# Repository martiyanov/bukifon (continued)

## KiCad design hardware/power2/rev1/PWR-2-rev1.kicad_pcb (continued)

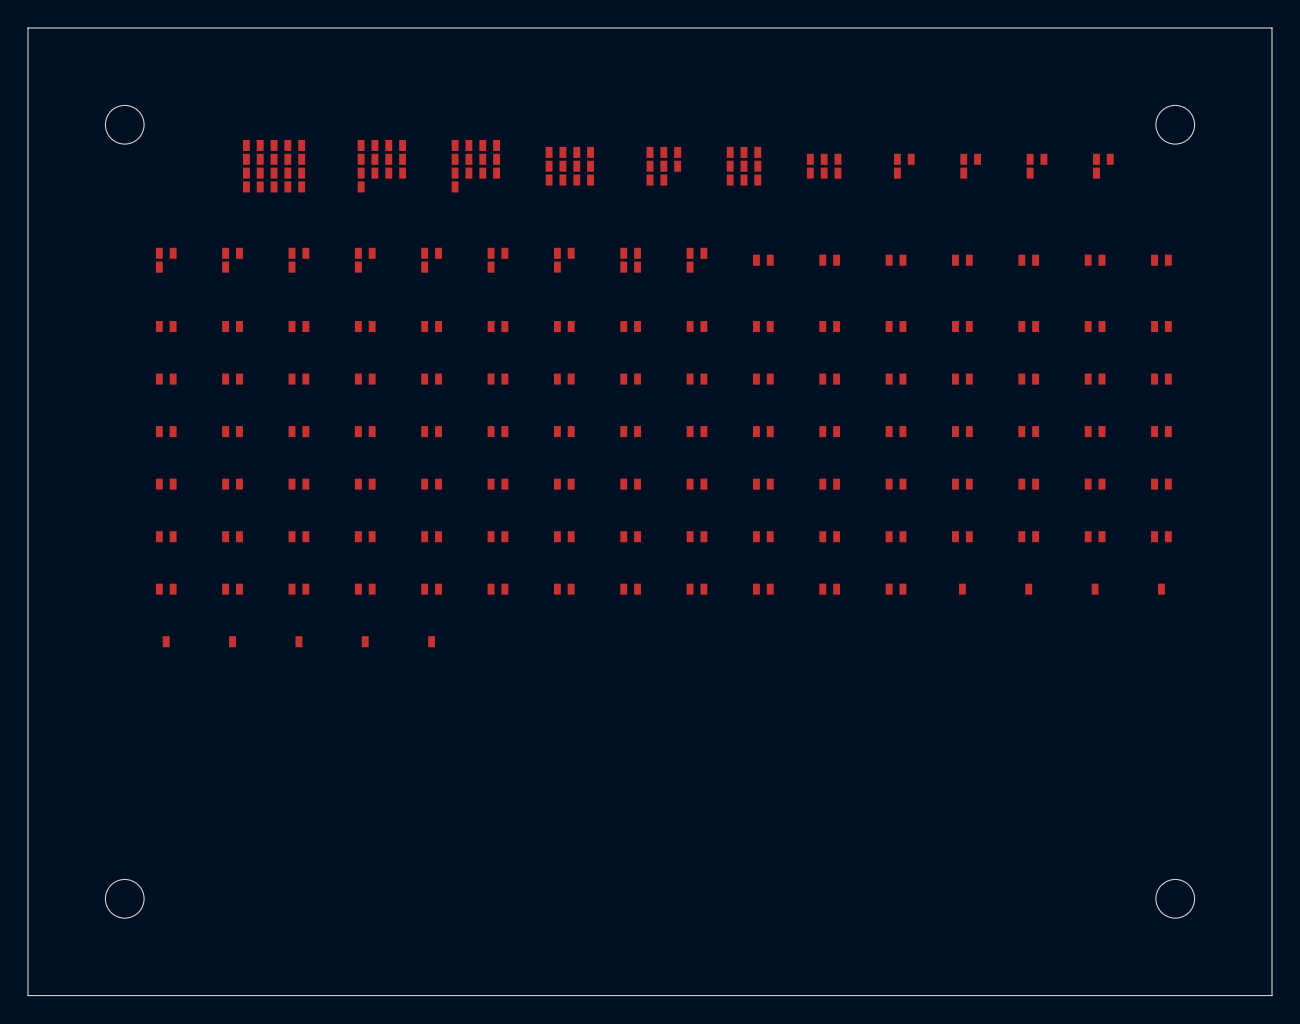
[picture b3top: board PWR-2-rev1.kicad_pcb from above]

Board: 4 copper layers, 90.0 x 70.0 mm, 132 parts (0 on the bottom side), 60 nets, no tracks yet.

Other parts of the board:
H1, H2, H3, H4: MountingHole; MountingHole_M2.5_2.8mm

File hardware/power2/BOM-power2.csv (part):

Артикул;MPN;Номинал;Кол-во;Позиции;Корпус;Примечание
PM-PWR2-001;;PACK 3P;1;J1;TerminalBlock_4Ucon_1x03_P3.50mm_Vertical;батарейный отсек: 1=B+, 2=B-, 3=NTC (термистор на банке)
PM-PWR2-002;;18650 3.6V 3.5Ah;1;BT1;BatteryHolder_Keystone_1042_1x18650;"банка 1/2 (параллель); холдер в батарейном отсеке, не на плате; off-board (battery/thermistor, вне платы)"
PM-PWR2-003;;18650 3.6V 3.5Ah;1;BT2;BatteryHolder_Keystone_1042_1x18650;"банка 2/2 (параллель); ХОЛДЕРЫ С КЛЮЧОМ от переполюсовки; off-board (battery/thermistor, вне платы)"
PM-PWR2-004;;5 A;1;F1;Fuse_1206_3216Metric;предохранитель пакета 4-5 А (по ТЗ): защита от КЗ и от переполюсовки одной банки
PM-PWR2-005;;AO3401A P-FET;1;Q1;SOT-23;защита от переполюсовки пакета: body diode PACK_F->VBAT (норма), reverse blocked
PM-PWR2-006;;100k;1;R1;R_0603_1608Metric;gate-source Q1: OFF при обрыве, ON при нормальной полярности (Vgs = -Vpack)
PM-PWR2-007;SMBJ5.0A;SMBJ5.0A;1;D1;D_SMA;TVS на пакете (ESD/импульсы при hot-plug)
PM-PWR2-008;;NTC 10k B3950;1;TH1;— (вне платы);"термистор на банке: -> TS BQ24074 (CORE-2) и -> CH7 (TEMP_MON); off-board (battery/thermistor, вне платы)"
PM-PWR2-009;;100R;1;R2;R_0603_1608Metric;RC-фильтр BAT BQ297xy
PM-PWR2-010;;100n;1;C1;C_0805_2012Metric;RC-фильтр BAT BQ297xy
PM-PWR2-011;;1k;1;R3;R_0603_1608Metric;токовый сенс BQ297xy (V-) к P-
PM-PWR2-012;BQ29700DSER (1S, OVP 4.275 В);BQ297xy;1;U1;SOT-23-6;BMS 1S: OVP 4.25-4.30 В, UVP 2.35-2.50 В, OCP/SCP (внешние NMOS)
PM-PWR2-013;AO3400A (N-FET 30 В);AO3400A;1;Q2;SOT-23;разрядный ключ BMS (общий исток с Q3)
PM-PWR2-014;AO3400A (N-FET 30 В);AO3400A;1;Q3;SOT-23;зарядный ключ BMS (общий исток с Q2)
PM-PWR2-015;;100k;1;R4;R_0603_1608Metric;gate-source Q2
PM-PWR2-016;;100k;1;R5;R_0603_1608Metric;gate-source Q3
PM-PWR2-017;;AO3401A P-FET;1;Q4;SOT-23;back-to-back P-FET 1/2 (reverse blocking, 11 мОм-класс)
PM-PWR2-018;;AO3401A P-FET;1;Q5;SOT-23;back-to-back P-FET 2/2
PM-PWR2-019;;100k;1;R6;R_0603_1608Metric;подтяжка затворов (OFF)
PM-PWR2-020;MMBT3904;MMBT3904;1;Q6;SOT-23;драйвер высокого плеча: ON = затворы к PGND
PM-PWR2-021;;10k;1;R7;R_0603_1608Metric;база Q6
PM-PWR2-022;;100k;1;R8;R_0603_1608Metric;база Q6 -> PGND (OFF по умолчанию)
PM-PWR2-023;;100k;1;R9;R_0603_1608Metric;MASTER_SW -> PGND (обрыв = OFF)
PM-PWR2-024;;100n;1;C2;C_0805_2012Metric;gate-source Q4/Q5: медленный пуск (inrush control)
PM-PWR2-025;;SW panel;1;J2;PinHeader_1x02_P2.54mm_Vertical;вывод на панельный тумблер питания (параллельно SW1)
PM-PWR2-026;;POWER OFF/ON;1;SW1;— (вне платы);местный слайдер питания (запасной/для макета)
PM-PWR2-027;SMBJ5.0A;SMBJ5.0A;1;D2;D_SMA;TVS после load switch
PM-PWR2-028;;22uF;1;C3;C_1210_3225Metric;вход всех преобразователей
PM-PWR2-029;MAX17048G+T (TDFN-8);MAX17048;1;U2;SOT-23-6;"fuel gauge 1S, I2C 0x36, +-7.5 мВ, без шунта; VDD = Kelvin на банку"
PM-PWR2-030;;10R;1;R10;R_0603_1608Metric;Kelvin-питание/сенс банки для гейджа (ток ~25 мкА)
PM-PWR2-031;;1uF;1;C4;C_0805_2012Metric;VDD гейджа
PM-PWR2-032;;100n;1;C5;C_0805_2012Metric;VDD гейджа ВЧ
PM-PWR2-033;;22R;1;R11;R_0603_1608Metric;серия I2C SDA (защита/развязка от длинного кабеля)
PM-PWR2-034;;22R;1;R12;R_0603_1608Metric;серия I2C SCL
PM-PWR2-035;;1k;1;R13;R_0603_1608Metric;резервный аналоговый контроль: сырой VBAT -> делитель CH6 на CORE-2
PM-PWR2-036;TPS61088RHLR (QFN-20);TPS61088;1;U3;QFN-20-1EP_3x3mm_P0.4mm_EP1.65x1.65mm;sync boost 10-A ключ: +12.15 В / 330 мА (запас 4x по току)
PM-PWR2-037;;10uH / 4A;1;L1;L_Bourns_SRN6045TA;индуктор +12 В (Isat >= 4 А)
PM-PWR2-038;;22uF;1;C6;C_1210_3225Metric;вход +12 В
PM-PWR2-039;;22uF;1;C7;C_1210_3225Metric;вход +12 В
PM-PWR2-040;;100n;1;C8;C_0805_2012Metric;вход +12 В ВЧ
PM-PWR2-041;;100k;1;R14;R_0603_1608Metric;ОС: Vout = 1.204*(1+100k/11k) = 12.15 В
PM-PWR2-042;;11k;1;R15;R_0603_1608Metric;низ ОС +12 В
PM-PWR2-043;;100n;1;C9;C_0805_2012Metric;soft-start +12 В
PM-PWR2-044;;100k;1;R16;R_0603_1608Metric;EN +12 В по умолчанию ON (pull-up в домене VSYS)
PM-PWR2-045;2N7002;2N7002;1;Q9;SOT-23;ключ EN +12 В: высокий уровень с CORE-2 (3.3 В) выключает рельс
PM-PWR2-046;;100n;1;C35;C_0805_2012Metric;фильтр EN +12 В
PM-PWR2-047;;4.7uH;1;L2;L_Bourns_SRN6045TA;pi-фильтр +12 В: L
PM-PWR2-048;;47uF/25V;1;C10;CP_Elec_6.3x7.7;pi-фильтр +12 В: C1
PM-PWR2-049;;47uF/25V;1;C11;CP_Elec_6.3x7.7;pi-фильтр +12 В: C2
PM-PWR2-050;;100n;1;C12;C_0805_2012Metric;pi-фильтр +12 В: HF
PM-PWR2-051;;0.5 A;1;F2;Fuse_1206_3216Metric;полифьюз шины +12 В (шина модулей <= 300 мА)
PM-PWR2-052;;SS34;1;D7;D_SMA;"последовательный SS34: защита от back-feed внешнего 12 В/шины; батарея не разряжается"
PM-PWR2-053;SMAJ15A;SMAJ15A;1;D3;D_SMA;TVS шины +12 В
PM-PWR2-054;;4.7k;1;R17;R_0603_1608Metric;разрядный резистор +12 В
PM-PWR2-055;;100n;1;C13;C_0805_2012Metric;ВЧ на шине +12 В
PM-PWR2-056;LMR33630ADDA (SOIC-8 PowerPAD, 36 В);LMR33630;1;U4;SOIC-8_3.9x4.9mm_P1.27mm;синхронный buck в инвертирующем IBB: GND МС = -12 В, VIN = VSYS+12 В = 15.7 В
PM-PWR2-057;;22uH / 2A;1;L3;L_Bourns_SRN6045TA;IBB: индуктор SW -> PGND (выход buck = системная земля)
PM-PWR2-058;;100n;1;C14;C_0805_2012Metric;bootstrap -12 В
PM-PWR2-059;;1uF;1;C15;C_0805_2012Metric;VCC МС (внутр. LDO) -> GND МС
PM-PWR2-060;;22uF/25V;1;C16;C_1210_3225Metric;вход IBB: 15.7 В (25 В керамика!)
PM-PWR2-061;;100n;1;C17;C_0805_2012Metric;вход IBB ВЧ
PM-PWR2-062;;22uF/25V;1;C18;C_1210_3225Metric;выход IBB 1
PM-PWR2-063;;22uF/25V;1;C19;C_1210_3225Metric;выход IBB 2
PM-PWR2-064;;110k;1;R19;R_0603_1608Metric;ОС IBB: Vout = 1.0*(1+110k/10k) = 12.0 В
PM-PWR2-065;;10k;1;R20;R_0603_1608Metric;низ ОС -12 В
PM-PWR2-066;PC817C (DIP-4);PC817;1;U5;DIP-4_W7.62mm;"оптопара: EN из домена PGND (3.3 В) в домен -12 В; транзистор тянет EN к GND МС"
PM-PWR2-067;;1k;1;R21;R_0603_1608Metric;ток LED оптопары ~2.1 мА
PM-PWR2-068;;100k;1;R22;R_0603_1608Metric;LED оптопары OFF при обрыве входа
PM-PWR2-069;;100k;1;R23;R_0603_1608Metric;EN -12 В по умолчанию ON (pull-up к VIN МС = 15.7 В)
PM-PWR2-070;;100n;1;C20;C_0805_2012Metric;фильтр EN -12 В
PM-PWR2-071;;10uH;1;L4;L_Bourns_SRN6045TA;pi-фильтр -12 В: L
PM-PWR2-072;;47uF/25V;1;C21;CP_Elec_6.3x7.7;pi-фильтр -12 В: C1
PM-PWR2-073;;47uF/25V;1;C22;CP_Elec_6.3x7.7;pi-фильтр -12 В: C2
PM-PWR2-074;;100n;1;C23;C_0805_2012Metric;pi-фильтр -12 В: HF
PM-PWR2-075;;0.3 A;1;F3;Fuse_1206_3216Metric;полифьюз -12 В (шина <= 95 мА)
PM-PWR2-076;;SS34;1;D8;D_SMA;последовательный SS34 (A=шина, K=преобразователь): защита -12 В от back-feed
PM-PWR2-077;SMAJ15A;SMAJ15A;1;D4;D_SMA;TVS -12 В
PM-PWR2-078;;4.7k;1;R24;R_0603_1608Metric;разрядный резистор -12 В
PM-PWR2-079;;100n;1;C24;C_0805_2012Metric;ВЧ на -12 В
PM-PWR2-080;TPS61088RHLR (QFN-20);TPS61088;1;U6;QFN-20-1EP_3x3mm_P0.4mm_EP1.65x1.65mm;sync boost: +5.10 В / 1.0 А (аудио, MIDI, логика, вход BL)
PM-PWR2-081;;10uH / 6A;1;L5;L_Bourns_SRN6045TA;индуктор +5 В: Iin до 3.8 А при 2 А/5.1 В и 3.0 В -> Isat >= 5.5 А
PM-PWR2-082;;22uF;1;C25;C_1210_3225Metric;вход +5 В
PM-PWR2-083;;22uF;1;C26;C_1210_3225Metric;вход +5 В
PM-PWR2-084;;100n;1;C27;C_0805_2012Metric;вход +5 В ВЧ
PM-PWR2-085;;100k;1;R25;R_0603_1608Metric;ОС: Vout = 1.204*(1+100k/30.9k) = 5.10 В
PM-PWR2-086;;30.9k;1;R26;R_0603_1608Metric;низ ОС +5 В
PM-PWR2-087;;100n;1;C28;C_0805_2012Metric;soft-start +5 В
PM-PWR2-088;;100k;1;R27;R_0603_1608Metric;EN +5 В по умолчанию ON
PM-PWR2-089;2N7002;2N7002;1;Q10;SOT-23;ключ EN +5 В: высокий уровень с CORE-2 выключает логическую шину
PM-PWR2-090;;100n;1;C38;C_0805_2012Metric;фильтр EN +5 В
PM-PWR2-091;;4.7uH;1;L6;L_Bourns_SRN6045TA;pi-фильтр +5 В: L
PM-PWR2-092;;47uF;1;C29;CP_Elec_6.3x7.7;pi-фильтр +5 В: C1
PM-PWR2-093;;47uF;1;C30;CP_Elec_6.3x7.7;pi-фильтр +5 В: C2
PM-PWR2-094;;100n;1;C31;C_0805_2012Metric;pi-фильтр +5 В: HF
PM-PWR2-095;;2 A;1;F4;Fuse_1206_3216Metric;полифьюз +5 В (логика/аудио/BL)
PM-PWR2-096;SMBJ5.0A;SMBJ5.0A;1;D5;D_SMA;TVS +5 В
PM-PWR2-097;;1k;1;R28;R_0603_1608Metric;разрядный резистор +5 В
PM-PWR2-098;;100n;1;C32;C_0805_2012Metric;ВЧ на +5 В
PM-PWR2-099;;2.5 A;1;F5;Fuse_1206_3216Metric;полифьюз LED-шины (74 WS2812, прошивочный cap)
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
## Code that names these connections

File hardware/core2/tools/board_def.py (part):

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 ('MIC_DATA', 42, 'I2S1 RX DATA (MEMS)', '3.3', 'in', 'none', 'low', 26, 'J19.5', 'ex-SD_D3; SDIO now 1-bit; J19 canon 5=DATA'),
 ('SD_CLK', 43, 'SDMMC SLOT0 CLK', '3.3', 'out', 'none', 'low', 27, 'J-SD.CLK', 'IO MUX SD1_CCLK'),
 ('SD_CMD', 44, 'SDMMC SLOT0 CMD', '3.3', 'bidir', '10k PU', 'high', 28, 'J-SD.CMD', 'IO MUX SD1_CCMD'),
 ('SD_CD', 45, 'GPIO in (card detect)', '3.3', 'in', '10k PU', 'high', 29, 'J-SD.DET', 'card detect switch to GND'),
 # --- I2S0 (audio DAC+ADC) ---
 ('I2S_MCLK', 20, 'I2S0 MCLK out', '3.3', 'out', 'none', 'low', 30, 'U9.SCK / U10.SCKI', '256fs = 12.288 MHz @48k'),
 ('I2S_BCK', 16, 'I2S0 BCK out', '3.3', 'out', 'none', 'low', 31, 'U9.BCK / U10.BCK', '64fs = 3.072 MHz @48k'),
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 ('LCD_R4', 47, 'LCD_CAM data R4', '3.3', 'out', 'none', 'low', 62, 'J-LCD.30', ''),
 ('BL_PWM', 49, 'LEDC PWM', '3.3', 'out', 'none', 'low', 16, 'J-LCD.31', 'backlight PWM -> panel BL driver'),
 # --- panel LED chain + IRQ + gates ---
 ('LED_GPIO', 48, 'RMT TX (WS2812)', '3.3 -> 5 V', 'out', 'none', 'low', 15, 'U-1G125.A', 'level shifter + 330R -> J-PANEL.11 LED_DATA'),
 ('PANEL_IRQ', 51, 'GPIO in', '3.3', 'in', '10k PU', 'high', 18, 'J-PANEL.9 / J-LCD.36', 'MCP23017 INTA (open drain)'),
 ('GATE1_GPIO', 52, 'GPIO out (2N7000)', '5.0 (open drain)', 'out', 'none', 'low', 19, 'J-PANEL.25 / BUS', '0/5 V gate, 4.7k PU to +5V_BUS'),
 ('GATE2_GPIO', 53, 'GPIO out (2N7000)', '5.0 (open drain)', 'out', 'none', 'low', 20, 'J-PANEL.26 / BUS', '0/5 V gate'),
 # --- ESP32-C6 coprocessor host link (Wi-Fi/BLE; SPI esp-hosted) ---
 ('C6_CS', 26, 'GP-SPI2 CS1', '3.3', 'out', '10k PU', 'high', 10, 'U-C6.SPI_CS', 'C6 select (shared SPI2)'),
 ('C6_HS', 24, 'GPIO (handshake)', '3.3', 'bidir', '10k PU', 'high', 11, 'U-C6.HANDSHAKE', 'esp-hosted SPI handshake'),
 ('C6_DR', 25, 'GPIO (data ready IRQ)', '3.3', 'in', '10k PU', 'high', 12, 'U-C6.DATA_READY', 'GPIO25 has USB_PU strap at reset (kept high)'),
 ('C6_RST', 27, 'GPIO out (C6 reset)', '3.3', 'out', '10k PD', 'low', 13, 'U-C6.EN', 'resets C6 at power-up; released by firmware'),
 # --- USB / power / strap ---
 ('BOOT', 35, 'boot strapping (GPIO35)', '3.3', 'in (strap)', '10k PU + button to GND', 'high (SPI boot)', 8, 'SW-BOOT', 'low at reset = joint download boot (USB HS / UART0)'),
 ('STRAP36', 36, 'boot strapping (GPIO36)', '3.3', 'in (strap)', '10k PU', 'high', 9, 'R96', 'needs 1 for joint download boot; 10k PU allows BOOT-button flashing'),
 ('MIC_SEL', 54, 'GPIO out (mic/line select)', '3.3', 'out', '100k PD', 'low', 14, 'U47.IN1/IN2', 'line=0 / mic=1; ex-VBUS_DET'),
 # --- dedicated / non-GPIO module pins ---
 ('USB_HS_DP', None, 'USB 2.0 HS OTG D+ (dedicated pin 50)', 'USB', 'bidir', 'USB internal', 'USB', 6, 'J-USB.A6/B6', 'through USBLC6-2SC6'),
 ('USB_HS_DM', None, 'USB 2.0 HS OTG D- (dedicated pin 49)', 'USB', 'bidir', 'USB internal', 'USB', 7, 'J-USB.A7/B7', 'through USBLC6-2SC6'),
 ('CHIP_PU', None, 'reset (CHIP_PU)', '3.3', 'in', '10k PU + 100nF', 'high', 5, 'SW-RESET', 'power-on reset, RC'),
 ('3V3_MCU', None, 'MCU/PSRAM supply', '3.3', 'power', '-', '-', 3, 'U26 out', 'MP1584 buck, separate rail'),
 ('3V3_MCU', None, 'MCU/PSRAM supply', '3.3', 'power', '-', '-', 4, 'U26 out', ''),
 ('GND', None, 'ground', '0', 'power', '-', '-', 1, 'GND', ''),
 ('GND', None, 'ground', '0', 'power', '-', '-', 2, 'GND', ''),
 ('LCD_DISP', 50, 'GPIO out (LCD power/enable)', '3.3', 'out', 'none', 'low', 17, 'J-LCD.37', 'display enable; final controllable GPIO'),
 ('GND', None, 'ground', '0', 'power', '-', '-', 63, 'GND', ''),
 ('GND', None, 'ground', '0', 'power', '-', '-', 64, 'GND', ''),
]
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 ('TP11', 'USB_HS_DP', 'USB D+'), ('TP12', 'USB_HS_DM', 'USB D-'),
 ('TP13', 'AGND', 'analog ground'), ('TP14', 'DGND', 'digital ground'),
 ('TP15', 'PGND', 'power ground'), ('TP16', 'LED_DATA', 'WS2812 data (after shifter)'),
 ('TP17', 'CHIP_PU', 'reset'), ('TP18', 'BOOT', 'boot strap GPIO35'),
 ('TP19', '3V3_C6', 'Wi-Fi/BLE coprocessor rail'), ('TP20', 'BL_20V', 'backlight rail'),
 ('TP21', 'C6_CS', 'C6 SPI select'), ('TP22', 'C6_RST', 'C6 reset'),
 ('TP23', 'N12_EXT', '-12 V input from PWR-2 (rev.2)'),
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# PANEL-2 expanders (on the panel board; documented here for the wiring table)
MCP23017 = [
 dict(addr='0x20', ref='U-P1', role='ENC1..ENC8 A/B (16 lines)',
      pins=['GPA0..GPA7 = ENC1_A..ENC8_A', 'GPB0..GPB7 = ENC1_B..ENC8_B', 'INTA -> PANEL_IRQ']),
 dict(addr='0x21', ref='U-P2', role='ENC9..ENC16 A/B (16 lines)',
      pins=['GPA0..GPA7 = ENC9_A..ENC16_A', 'GPB0..GPB7 = ENC9_B..ENC16_B', 'INTA -> PANEL_IRQ']),
 dict(addr='0x22', ref='U-P3', role='16 encoder push buttons (16 lines)',
      pins=['GPA0..GPA7 = ENC1_PUSH..ENC8_PUSH', 'GPB0..GPB7 = ENC9_PUSH..ENC16_PUSH',
            'INTA -> PANEL_IRQ']),
 dict(addr='0x23', ref='U-P4', role='42-key matrix 6x7 (13 lines) + 2 EN lines (rev.2)',
      pins=['GPA0..GPA6 = COL0..COL6 (inputs, 10k PU)',
            'GPB0..GPB5 = ROW0..ROW5 (outputs, scan)',
            'GPA7 = EN_RAILS (rev.2, active-high disable +12/-12/+5)',
            'GPB6 = EN_LED5 (rev.2, active-high enable; default OFF)',
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]
# display contract
DISPLAY = dict(interface='LCD_CAM parallel RGB565 (16-bit) + PCLK/DE/HSYNC/VSYNC',
               resolution='800x480', pins='25 signals: 20 LCD + I2C(2) + INT + BL_PWM + DISP (+BL_ANODE/BL_CATHODE)',
               connector='J-LCD (FFC-40, 0.5 mm; PANEL-2 J12) + J-PANEL (IDC-26; J14)',
               bl='BL_ANODE/BL_CATHODE from CORE-2 +20 V boost, BL_PWM (LEDC) to panel driver',
               disp='LCD_DISP on GPIO50 (last free GPIO); active-high enable')
AUDIO = dict(fs='48 kHz (44.1 kHz also supported by PLL)',
             mclk='12.288 MHz = 256 fs', bck='3.072 MHz = 64 fs', lrck='48 kHz',
             dac='PCM5102A, I2S, 24-bit, SCK = shared MCLK', dac_cfg='FMT=0 (I2S), DEMP=0, FLT=0, XSMT=1 (unmute via 10k PU)',
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
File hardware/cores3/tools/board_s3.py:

# -*- coding: utf-8 -*-
"""CORE-S3 board data: GPIO budget, connectors, rails, comparison (PRE-FREEZE)."""

# GPIO budget: ESP32-S3-WROOM-1-N16R8. Usable module GPIO = 31
# (GPIO0-18, 21, 38-48; GPIO19/20 = USB, GPIO26-32 flash, GPIO33-37 octal PSRAM).
PINMAP = [
 ('LCD_SCK', 12, 'SPI2 FSPICLK (IOMUX)', 'out', 'SPI display prototytpe variant'),
 ('LCD_MOSI', 11, 'SPI2 FSPID (IOMUX)', 'out', ''),
 ('LCD_CS', 10, 'SPI2 FSPICS0', 'out', ''),
 ('LCD_DC', 9, 'GPIO', 'out', ''),
 ('LCD_RST', 8, 'GPIO', 'out', ''),
 ('BL_PWM', 21, 'LEDC PWM', 'out', 'backlight PWM -> BL boost'),
 ('SPI3_SCK', 4, 'SPI3 SCK (matrix)', 'out', 'MCP3208, 10 MHz'),
 ('SPI3_MOSI', 5, 'SPI3 MOSI', 'out', ''),
 ('SPI3_MISO', 6, 'SPI3 MISO', 'in', 'MCP3208 DOUT'),
 ('MCP3208_CS', 7, 'SPI3 CS0', 'out', ''),
 ('SD_CLK', 15, 'SDMMC CLK', 'out', 'microSD 1-bit SDMMC'),
 ('SD_CMD', 14, 'SDMMC CMD', 'bidir', ''),
 ('SD_D0', 13, 'SDMMC D0', 'bidir', ''),
 ('I2C0_SDA', 16, 'I2C0 SDA', 'bidir', 'MCP4728 x2, 24C32, PANEL-2'),
 ('I2C0_SCL', 17, 'I2C0 SCL', 'out', '400 kHz'),
 ('I2S_MCLK', 18, 'I2S0 MCLK', 'out', '12.288 MHz = 256 fs'),
 ('I2S_BCK', 1, 'I2S0 BCK', 'out', '3.072 MHz'),
 ('I2S_LRCK', 2, 'I2S0 WS', 'out', '48 kHz'),
 ('I2S_DAC_DIN', 38, 'I2S0 SD_OUT', 'out', 'PCM5102A'),
 ('I2S_ADC_DOUT', 39, 'I2S0 SD_IN', 'in', 'PCM1808'),
 ('MIDI_TX', 40, 'UART1 TX (matrix)', 'out', '74HCT125'),
 ('MIDI_RX', 41, 'UART1 RX (matrix)', 'in', '6N137'),
 ('LED_DATA', 42, 'RMT', 'out', 'WS2812 (level shifter on PANEL-2)'),
 ('PANEL_IRQ', 47, 'GPIO in', 'in', '4x MCP23017 INTA (10k PU)'),
 ('GATE1_GPIO', 48, 'GPIO', 'out', '2N7000 gate out (GATE2 dropped)'),
 ('PWR_GOOD', 3, 'GPIO in', 'in', 'PWR-2 supervisor (100k PU)'),
 ('BOOT', 0, 'GPIO / strapping', 'in', 'BOOT button (USB-JTAG also available)'),
]
FREE_GPIO = [3, 13, 45, 46]
USB_PINS = ['USB_D-', 'USB_D+']
STRAP_PINS = [0, 3, 45, 46]

# PANEL-2 rev.2 canon (same as CORE-2 rev.2)
J14_PANEL = [(1,'CVOUT1'),(2,'AGND'),(3,'CVOUT2'),(4,'AGND'),(5,'CVOUT3'),(6,'AGND'),
 (7,'CVOUT4'),(8,'AGND'),(9,'CVIN1'),(10,'AGND'),(11,'CVIN2'),(12,'AGND'),
 (13,'CVIN3'),(14,'AGND'),(15,'CVIN4'),(16,'AGND'),(17,'GATE1'),(18,'AGND'),
 (19,'NC'),(20,'AGND'),(21,'FADER1'),(22,'AGND'),(23,'FADER2'),(24,'AGND'),
 (25,'EN_LED5'),(26,'AGND')]
J16_PANEL = [(1,'I2C0_SDA'),(2,'DGND'),(3,'I2C0_SCL'),(4,'DGND'),(5,'PANEL_IRQ'),(6,'DGND'),
 (7,'LED_DATA'),(8,'DGND'),(9,'5V_LED'),(10,'DGND'),(11,'3V3_PANEL'),(12,'DGND'),
 (13,'5V_LED'),(14,'DGND'),(15,'EN_RAILS'),(16,'LED_RET')]
# J15 FFC-40: mechanical PANEL-2 J12 connector, but CORE-S3 uses SPI panel (partial UI)
J15_DISPLAY = [(1,'DGND'),(2,'DGND'),(3,'LCD_SCK'),(4,'LCD_MOSI'),(5,'LCD_CS'),(6,'LCD_DC'),
 (7,'LCD_RST'),(8,'BL_PWM'),(9,'3V3_PANEL'),(10,'DGND'),(11,'BL_20V'),(12,'BL_CATHODE'),
 (13,'DGND'),(14,'DGND'),(15,'DGND'),(16,'DGND'),(17,'DGND'),(18,'DGND'),(19,'DGND'),(20,'DGND'),
 (21,'DGND'),(22,'DGND'),(23,'DGND'),(24,'DGND'),(25,'DGND'),(26,'DGND'),(27,'3V3_PANEL'),
 (28,'3V3_PANEL'),(29,'DGND'),(30,'DGND'),(31,'DGND'),(32,'DGND'),(33,'DGND'),(34,'DGND'),
 (35,'DGND'),(36,'DGND'),(37,'DGND'),(38,'DGND'),(39,'DGND'),(40,'DGND')]
J17_PWR3 = [(1,'VSYS'),(2,'VSYS'),(3,'BATT_P'),(4,'BATT_P'),(5,'12V_EXT'),(6,'12V_EXT'),
 (7,'PGND'),(8,'PGND'),(9,'N12_EXT'),(10,'N12_EXT'),(11,'PGND'),(12,'PGND'),
 (13,'5V_EXT'),(14,'5V_EXT'),(15,'PGND'),(16,'PGND'),(17,'5V_LED'),(18,'LED_RET'),
 (19,'PGND'),(20,'PGND')]
J18_PWR4 = [(1,'BATT_MON_RAW'),(2,'NTC_PACK'),(3,'I2C0_SDA'),(4,'I2C0_SCL'),(5,'FUEL_ALRT'),
 (6,'PWR_GOOD'),(7,'EN_BUS12'),(8,'EN_N12'),(9,'EN_LED5'),(10,'EN_5V'),(11,'PGND'),(12,'PGND')]

RAILS = [
 dict(name='+3V3 (TPS63000 buck-boost)', src='VSYS 3.0...4.4 V', bud=700, cap=1000,
      margin=30, loads='S3 350 + PSRAM 50 + panel logic 150 + audio 60 + CV 30 + MIDI 10 + misc 50'),
 dict(name='+5V (PWR-2 J3)', src='PWR-2 5.10 V', bud=290, cap=1600,
      margin=82, loads='PCM1808 VCC 30 + MIDI 10 + BL-boost input 80 + panel 5V 170 (5V_LED)'),
 dict(name='+12V (PWR-2 J3)', src='PWR-2 11.7 V', bud=150, cap=330, margin=55,
      loads='module bus 2x60 + opamps 30'),
 dict(name='-12V (PWR-2 J3)', src='PWR-2 -11.55 V', bud=95, cap=95, margin=0,
      loads='module bus 2x40 + opamps 15; budget = limit, exception'),
 dict(name='BL_20V (MT3608 #3)', src='+5V', bud=30, cap=100, margin=70,
      loads='LCD backlight LED string 20-25 mA'),
]
COMPARISON = [
 ('MCU', 'ESP32-P4 (RISC-V 400 MHz, 32 MB PSRAM) + ESP32-C6 (Wi-Fi 6/BLE 5.3)', 'ESP32-S3-WROOM-1-N16R8 (Xtensa LX7 240 MHz, 16 MB flash, 8 MB octal PSRAM), Wi-Fi 4/BLE 5.0 onboard'),
 ('USB', 'HS 480 Mbps, composite HID+MIDI+UAC2+CDC', 'FS 12 Mbps, composite HID+MIDI+UAC1/2 stereo+CDC (8x8 UAC2 NOT supported)'),
 ('Display', 'RGB565 800x480, 20 GPIO, up to 60 fps', 'SPI 800x480 16-bit, 6 GPIO, full frame ~12-15 fps, partial UI 10-20 fps'),
 ('DSP', 'Dual DSP extensions, 360 DMIPS+, 32 MB PSRAM', 'Xtensa LX7 + vector ops, 8 MB PSRAM; 8 mono voices / 6 polyphonic with effects'),
 ('Wi-Fi/BLE', 'C6 coprocessor over SPI (esp-hosted)', 'native Wi-Fi 4 / BLE 5.0; no C6 board/keep-out/LDO'),
 ('SD card', 'SDIO 4-bit', 'SPI mode on shared SPI3 bus (~10-20 MB/s)'),
 ('Power', '+3V3 via AP2112K + MP1584 + AP2112K(+3V3_C6); +5/+-12 from PWR-2', '+3V3 via single TPS63000 buck-boost from VSYS (no MP1584/LDOs/C6 rail)'),
 ('Connectors', 'J14/J15/J16 PANEL-2 + J17/J18 PWR-2', 'same J14/J13/J12 (J15 FFC-40) + J17/J18 (panel J12 pinout used for SPI subset)'),
 ('BOM cost (est.)', 'higher: P4+C6 modules, HS crystal/ESD, 2 extra LDOs', 'lower: one S3 module (~$8-12), no C6/LDOs; board est. $45-65, kit $199 target'),
 ('Firmware', 'ESP-IDF P4 + esp-hosted RPC', 'ESP-IDF S3; shared UI/audio layers; some P4 DSP paths reduced'),
]

SECTIONS = {
 'POWER': 'POWER: USB-C + BQ24074 charge/path, TPS63000 3V3 buck-boost (D-41), +-12V/+5V from PWR-2 J17, BL boost',
 'MCU': 'MCU: ESP32-S3-WROOM-1-N16R8 (USB FS, 8 MB PSRAM), microSD SPI, BOOT/RESET, UART0 TP',
 'AUDIO': 'AUDIO: PCM5102A DAC + PCM1808 ADC (I2S), TL072 LINE/PHONES, rear jacks',
 'CV': 'CV: 2x MCP4728 (0x60/0x61), 6x TL074 x4.9, CV IN level shift (1-4), MCP3208 + chains',
 'MIDI': 'MIDI TRS-A: 6N137 IN / 74HCT125 OUT; GATE_OUT driver',
 'BUS': 'MODULE BUS: 2x IDC-26 analog bus (+-12V, CV1..4, GATE, audio), per-port protection',
 'PANEL': 'PANEL-2 rev.2 canon: J14 IDC-26 analog, J15 FFC-40 SPI display, J16 IDC-16 digital; rear jacks; J17/J18 PWR-2',
 'TP': 'TEST POINTS (TP1..TP22)',
}
